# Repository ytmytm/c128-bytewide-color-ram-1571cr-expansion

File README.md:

# C128 8-bit Color RAM and C128DCR 1571CR RAM expansion

This is a 24 to 28 pin adapter PCB that can be used for three different C128 modifications:

- widen 2K Color RAM to 8 bits (C128/C128D/C128DCR)
- widen Color RAM to 8 bits and expand to 32K (C128/C128D/C128DCR)
- RAM Expansion for 1571CR compatible with Maverick (C128DCR only)

## Schematic

PDF plot of [the schematic can be found here](kicad/plots/kicad-c128-byte-wide-color-ram.pdf).

[kicad](kicad/) folder contains all the KiCad 6.0 project files.

## PCB

[kicad/plots](kicad/plots) folder contains Gerber files for manufacturing a PCB for any of these projects.

# 8-bit Color RAM

## Background

The idea comes from [a project published in 1990](http://www.sdiy.org/richardc64/color/byte.html).

All C128 variations use 8x2K SRAM chip (2016) for Color RAM. Although RAM is 8-bit, only lower 4 bits are connected. Lines D4-D7 are pulled up by a resistor pack to 5V.
This project replicates part of the onboard circuit and adds a quad switch 4066 as a bidirectional buffer between higher 4 bits and CPU bus.
Like the onboard U20 (4066) it switches Color RAM on/off bus, depending on the state of AEC line.

Note: this schematic shows the general idea. Don't cut anything on the mainboard and don't piggyback chips

## Why?

For sure it doesn't add any colors. However having 1K (2K in C128 mode) of additional RAM may be useful for some projects. It is compatible with any other expansion or cartidge.

## 32K option

Even more of that RAM? Possibilities are endless, but how to switch the banks?

VIC utilizes 1K of Color RAM, but C128 was equipped with double of that amount to support split screen multicolor graphics in BASIC. The bank switching between lower 1K and upper 1K is done using CPU port at location $01.
In C64 mode this port decides about RAM/ROM configuration, in C128 mode lower two bits determine which half of 2K Color RAM is seen by VIC and which half by CPU.

It only made sense to me to extend this further and use other $01 port bits to provide more address lines for 32K Color RAM expansion. None of my C128s will be ever used with tape (or even TapeCart), so I connected A11-13 lines to
lines normally used by tape motor control, tape write and sense bits. This provides 13 bits of address, so 16K total.

You don't need to connect all of them or you can skip it altogether. I have reused connections to onboard pull-up resistors to pull these address lines high if nothing is connecte to the solder pads.

Until I have a better idea where to connect A14 I will be happy with using 16K of that RAM. That's enough for 16 full screens: 8 for imaginary FLI mode with color ram switched every line and another 8 for interlaced option.

Note that a lot of C64 software will write to CPU port ($01) location and can modify the status of tape control bits. If you're not planning to use tape device I highly recommend patching the ROM (details below)
to set these bits as input by default. This completely removes the problem as virtually no software modifies CPU port direction register ($00).

## Assembly

Parts needed:

- 24-pin socket to be soldered in place of removed U19
- two sets of 12 round pins (24 total)
- 4066 analog quad switch and 14-pin socket for it
- 24-pin socket for 2K SRAM (2016) *or* 28-pin socket for 32K SRAM (62256)
- 8x2K RAM (ideally 2016 desoldered from the board) *or* 8x32K SRAM (62256)

In any case you need to remove or desolder the original 2K chip (U19) and replace it by a 24-pin socket. PCB is meant to be equipped with round pins and plugged into that socket.
We also need some signals from the board, so additional wires will be needed.

Start assembly by soldering in two rows of 24 round pins that will be used to plug in PCB to the C128/D/DCR mainboard.
For this project you need to solder them in the row of holes closest to the PCB edge and the one marked on silkscreen, on the image below marked by RED.

For 2K option solder the 24-pin socket in holes marked GREEN. For 32K option solder 28-pin socket in holes marked YELLOW.

The last step of the assembly is soldering in 14-pin socket for 4066.

## Installation

Once the assembled PCB is plugged into place of original SRAM (U19) (*mind the orientation*) you need to connect five additional wires to the mainboard:

- connect AEC from onboard U20 (4066) any pin 5, 6, 12 or 13 - they are all connected together
- connect D4-D7 in any order from charset ROM nearby or from convenient vias. You may have 24 or 28-pin ROM there, so check the pinout and verify against e.g. CPU

D4-D7 lines are on the right bottom end of the chip.

**Note:** if you don't have 2K SRAM chip or it was damaged during desoldering you can just pop in 32K SRAM chip (still available these days) and stop here.
If you look on the schematics I have routed onboard D4-D7 lines (pulled high by onboard resistors) to A11-A14 lines.
So if you don't connect there anything at all they will be driven high and even with 32K SRAM those 2K of Color RAM will be available with no extra connections.

## Installation (32K Color RAM)

- connect A11/A12/A13 to CPU tape ports P3/P4/P5 from CPU socket (pins 27/26/25) or from convenient vias

Like with data lines it doesn't really matter in which order you connect those tape motor/write/sense connections to solder points A11-A14 lines or even if you leave A11 or A14 unconnected.

I wanted to avoid soldering directly to CPU (or underneath CPU) even though I have it already socketed. Instead I found several vias for convenient access.

For C128/C128D I found it invaluable to open [C128 Neo project in KiCad](https://github.com/jgrip/open128) and highlight ports and their net (using `` key) to see where they cross the board sides.

Here is how it can look like on C128D. It's already a mess off wires on that machine but you get the general idea:

- YELLOW points show AEC connection to U20
- ORANGE points show A11/A12/A13 connections to two vias and one side of R4 resistor
- A14 is not connected to anything
- data lines D4-D7 are connected to character ROM adapter nearby

## Testing

In C128 mode in monitor try:

```
M FD800 FD8080
```

then edit some values and try issuing the command again. You should see that the top four bits (first hex digit) hold their value.

## Testing (32K Color RAM)

Extra address lines are controlled by CPU port. First let's switch them all to output (as tape sense is an input by default):

```
POKE 0, PEEK(0) OR (8+16+32)
```

Then try to put some colored text on screen and switch RAM banks back and forth by using various combinations of bits 3, 4 and 5

```
X = PEEK(1) AND 199
POKE 1, X
POKE 1, X OR 8
POKE 1, X OR (8+16)
POKE 1, X OR 32
...
```

## Patching ROM (32K Color RAM)

C64/128 ROM will set the CPU port direction register ($00) to value $2F. This sets up bits 5 and 3 as outputs because they control tape motor and tape write lines. However a lot of C64 software will write to CPU port ($01)
and modify bits 3/4/5 that we allocated to select Color RAM banks. This doesn't break anything but may cause flicker or random screen colors during some operations (e.g. decompressing) - as if Color RAM was faulty.

An easy way to fix this is to patch Kernal C64 and C128 to set $00 to make all bits 3/4/5 as inputs by default. This can be easy accomplished with a hex editor such as [HxD](https://mh-nexus.de/en/hxd/).

For a 32K ROM for C128DCR (U32), or C128D modified to use 32K chips, use this already patched file: [U32.complete.318023-02-patched.bin](rom/U32.complete.318023-02-patched.bin).

1. Dump from onboard chips (or download from [zimmers.net](http://www.zimmers.net/anonftp/pub/cbm/firmware/computers/c128/index.html) ROM appropriate to your C128: 16K for unmodified C128D or 32K for C128DCR

2. Use hex editor to patch the ROM - search for values `A9 2F 85 00` and replace `2F` by `07`. In American ROM (complete.318023-02.bin) that value appears at offsets:

- `$3DDA` - C64 Kernal soft reset (real address `$FDDA`)
- `$613D` - C128 Kernal soft reset (real address `$FE13D`)
- `$6250` - C128 Kernal GO64 (real address `$FE250`)

3. If you have JiffyDOS or a 64K ROM with a switch that value will appear three more times in the second 32K half of the ROM. Patch it as well from `2F` to `07`.

4. Save and flash into a new EEPROM to replace onboard ROM U32 (DCR)

## Patching VICE (32K Color RAM)

If you can recompile [VICE](https://vice-emu.sourceforge.io/) on your own, here is a patch to enable 32K Color RAM emulation.

[ytm-c128-colorram-expansion.patch](vice/ytm-c128-colorram-expansion.patch)

This is based off VICE 3.8 release (28 December 2023, revision 44935).

You will find new option in `Settings -> Machine -> Mode -> Miscellaneous -> Expand color RAM...`.

This can be passed also from command line via `-c128colorramexpansion` option.

# 1571CR RAM expansion

## Background

Since I already had this PCB, which also does 2K (24 pin) to 32K (28 pin) conversion I had a closer look on the second 2016 2K SRAM chip present on C128DCR board.

This is 1571 RAM. In standard configuration there are exactly 2K of SRAM in range $0000-$07FF, just like on 1541.

There are [several projects that expand RAM on external 1571 and 1541s](http://d81.de/CLD-RAMBOard/References.shtml), but I couldn't find anything for 1571CR (internal 1571 of C128DCR).

I found a [memory map on zimmers.net](http://www.zimmers.net/anonftp/pub/cbm/schematics/drives/new/1571/memorymap.txt)
that described $6000-$7FFF range as "RAM shadows", so I conducted an experiment.

I have removed U103 (2016 2K SRAM) and put in this place a 24 to 28 pin adapter for 62256 (32K SRAM) and I connected A11-A14 directly to U101 (6502 CPU).
It worked right away with no extra parts. I was able to copy disks with Maverick v5 RAMBoard nibbler.

After more testing I saw that RAM is actualy present also in $0800-$0FFF range. In both $0000-$0FFF and $6000-$7FFF ranges that provides a total of 12K available.

## Why?

The only purpose seems to be [Maverick v5 RAMBoard nibbler](https://csdb.dk/release/?id=18107). [DolphinDOS uses extra memory](https://e4aws.silverdr.com/projects/dolphindos3/) but there is no way to add a parallel port to 1571CR in a way DolphinDOS expects - all these VIA port lines are
already used.

In Maverick to go 'GCR Nibbler' option and choose 'RAMBoard'. In further settings choose $6000-$7FFF area for RAM.

## Assembly

Parts needed:

- 24-pin socket to be soldered in place of removed U103
- two sets of 12 round pins (24 total)
- 28-pin socket for 32K SRAM (62256)
- 8x32K SRAM (62256)

You need to remove or desolder the original 2K chip (U103) and replace it by a 24-pin socket. PCB is meant to be equipped with round pins and plugged into that socket.
We also need some signals from the board, so additional wires will be needed.

Start assembly by soldering in two rows of 24 round pins that will be used to plug in PCB to the C128DCR mainboard.

For this project you need to leave RED holes unoccupied and solder round pins in the middle row of holes from the PCB edge, on the image below marked by GREEN.

Solder 28-pin socket in holes marked YELLOW. You don't need to do anything about 14-pin 4066 either, that won't be used.

Here is how it looks like. Don't mind the orange and yellow wires. These are jumpers that I missed to route in the first version of the board. Current project has it already fixed.

## Installation

Once the assembled PCB is plugged into place of original SRAM (U103) (*mind the orientation*) you need to connect four additional wires to the mainboard: the new address lines.

In the prototype I soldered them directly to the CPU (U101) pins 20, 22, 23 and 24, but I don't like this solution in the long run:

There are four vias where these address lines can be found:

## Testing

You can use test program from [RAMBOard test/demo disk](media/ramboard.zip) (cached from http://d81.de/CLD-RAMBOard/refs/ramboard.zip). For whatever reason the test program works but disk copier doesn't.

If you have JiffyDOS, it's easy to use JiffyMon in C64 mode. It can be [downloaded from CSDB](https://csdb.dk/release/?id=16906) with [PDF manual available here](http://slark.me/c64-downloads/jiffymon-machine-language-monitor-users-guide.pdf)

Commands with asterisk will act on the default drive memory, like:
```
M* 6000 6080
```
or copy data between C128 and the drive - from range $6000-$6080 to $0400 (top of screen):
```
MR 6000 6080 0400
```
and back from computer to the drive:
```
MW 0400 0480 6000
```

Restart monitor with
```
SYS 64715
```

For actual disk copying get Maverick V5 and after choosing GCR Nibbler select RAMBOard option. Then set it up for RAM that starts at $6000.

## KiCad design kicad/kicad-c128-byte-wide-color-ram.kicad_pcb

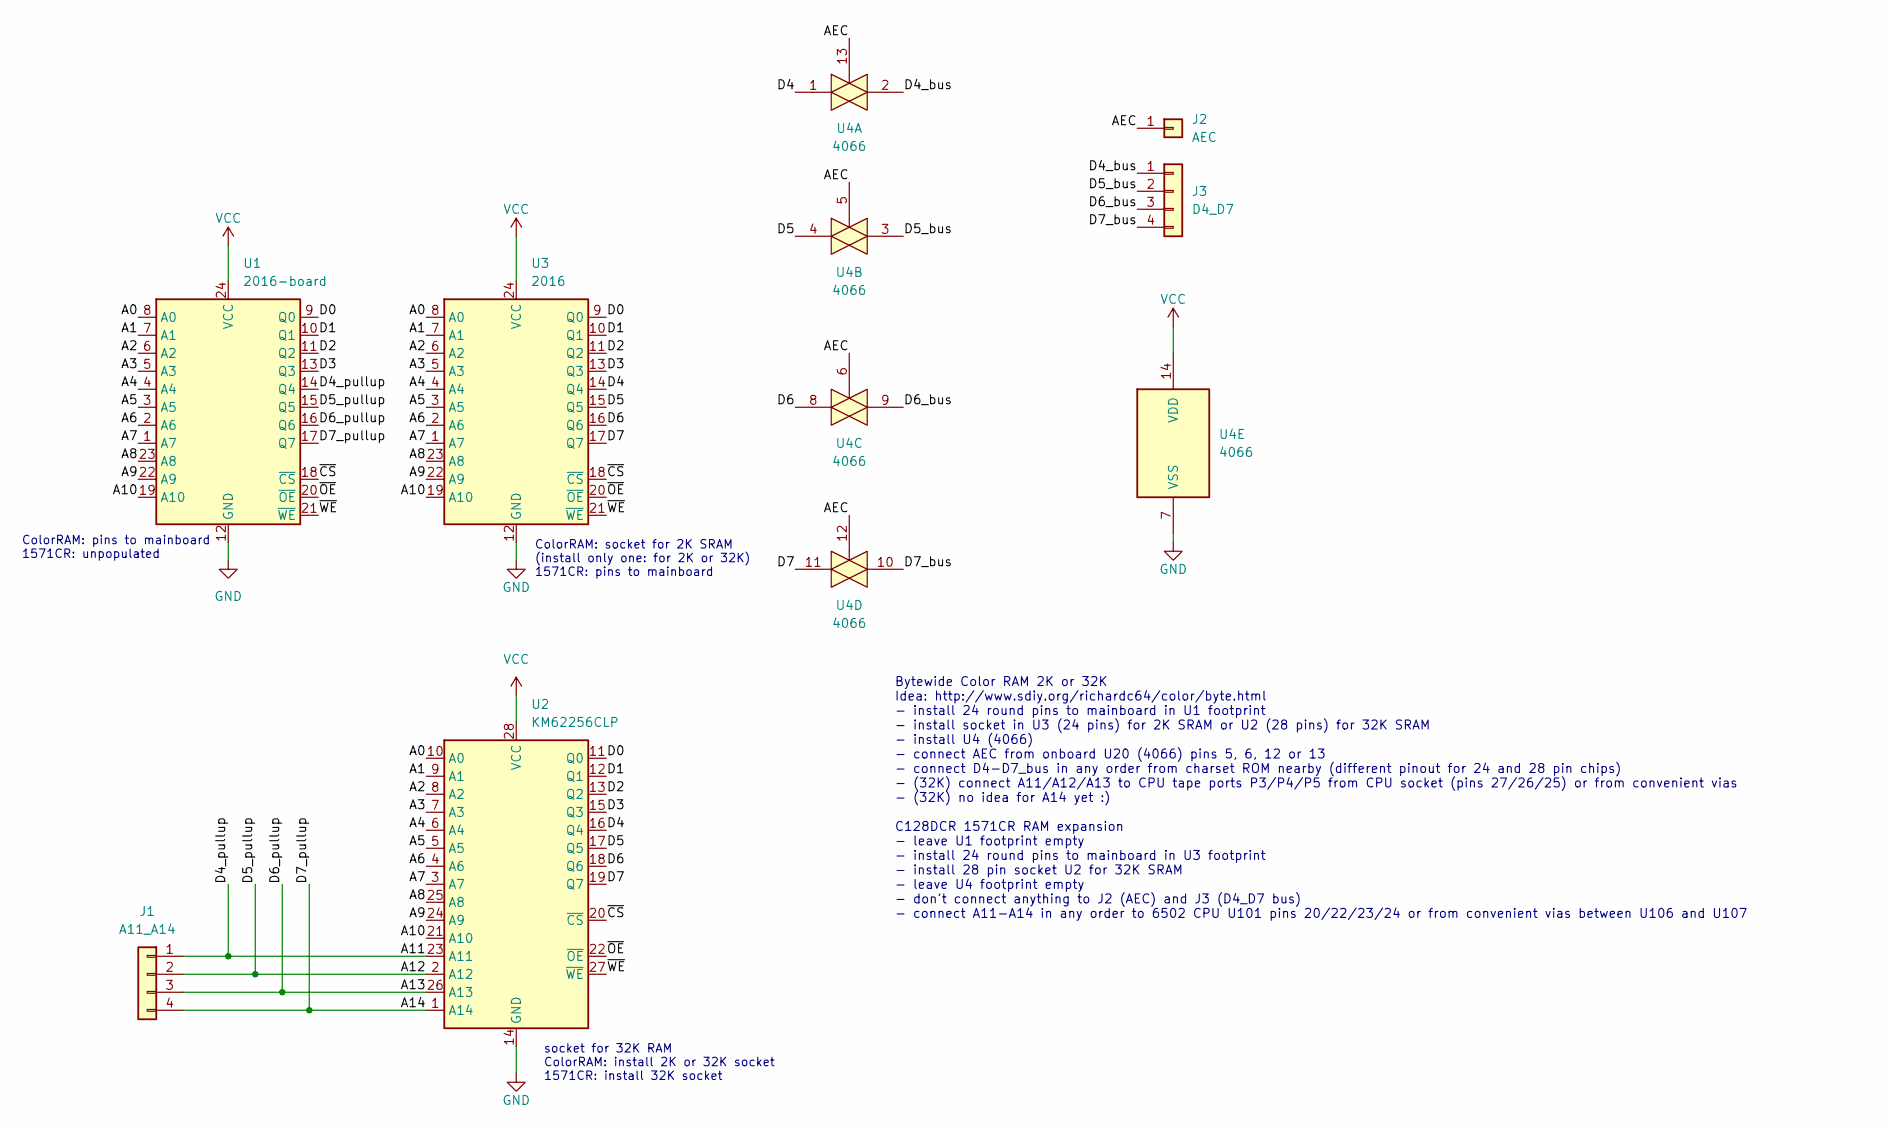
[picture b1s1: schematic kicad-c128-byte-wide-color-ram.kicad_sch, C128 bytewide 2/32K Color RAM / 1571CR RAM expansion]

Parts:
J1: A11_A14; PinHeader_1x04_P2.54mm_Vertical
J2: AEC; PinHeader_1x01_P2.54mm_Vertical
J3: D4_D7; PinHeader_1x04_P2.54mm_Vertical
U1: 2016-board; DIP-24_W15.24mm
U2: KM62256CLP; DIP-28_W15.24mm
U3: 2016; DIP-24_W15.24mm
U4: 4066; DIP-14_W7.62mm_Socket

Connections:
/A0: U1.8 (A0), U2.10 (A0), U3.8 (A0)
/A1: U1.7 (A1), U2.9 (A1), U3.7 (A1)
/A2: U1.6 (A2), U2.8 (A2), U3.6 (A2)
/A3: U1.5 (A3), U2.7 (A3), U3.5 (A3)
/A4: U1.4 (A4), U2.6 (A4), U3.4 (A4)
/A5: U1.3 (A5), U2.5 (A5), U3.3 (A5)
/A6: U1.2 (A6), U2.4 (A6), U3.2 (A6)
/A7: U1.1 (A7), U2.3 (A7), U3.1 (A7)
/A8: U1.23 (A8), U2.25 (A8), U3.23 (A8)
/A9: U1.22 (A9), U2.24 (A9), U3.22 (A9)
/A10: U1.19 (A10), U2.21 (A10), U3.19 (A10)
/A11: J1.1, U1.14 (Q4), U2.23 (A11)
/A12: J1.2, U1.15 (Q5), U2.2 (A12)
/A13: J1.3, U1.16 (Q6), U2.26 (A13)
/A14: J1.4, U1.17 (Q7), U2.1 (A14)
/AEC: J2.1, U4.5, U4.6, U4.12, U4.13
/D0: U1.9 (Q0), U2.11 (Q0), U3.9 (Q0)
/D1: U1.10 (Q1), U2.12 (Q1), U3.10 (Q1)
/D2: U1.11 (Q2), U2.13 (Q2), U3.11 (Q2)
/D3: U1.13 (Q3), U2.15 (Q3), U3.13 (Q3)
/D4: U2.16 (Q4), U3.14 (Q4), U4.1
/D4_bus: J3.1, U4.2
/D5: U2.17 (Q5), U3.15 (Q5), U4.4
/D5_bus: J3.2, U4.3
/D6: U2.18 (Q6), U3.16 (Q6), U4.8
/D6_bus: J3.3, U4.9
/D7: U2.19 (Q7), U3.17 (Q7), U4.11
/D7_bus: J3.4, U4.10
/~CS: U1.18 (~CS), U2.20 (~CS), U3.18 (~CS)
/~OE: U1.20 (~OE), U2.22 (~OE), U3.20 (~OE)
/~WE: U1.21 (~WE), U2.27 (~WE), U3.21 (~WE)
GND: U1.12 (GND), U2.14 (GND), U3.12 (GND), U4.7 (VSS)
VCC: U1.24 (VCC), U2.28 (VCC), U3.24 (VCC), U4.14 (VDD)

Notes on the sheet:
Bytewide Color RAM 2K or 32K Idea: http://www.sdiy.org/richardc64/color/byte.html - install 24 round pins to mainboard in U1 footprint - install socket in U3 (24 pins) for 2K SRAM or U2 (28 pins) for 32K SRAM - install U4 (4066) - connect AEC from onboard U20 (4066) pins 5, 6, 12 or 13 - connect D4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
ColorRAM: socket for 2K SRAM (install only one: for 2K or 32K) 1571CR: pins to mainboard
socket for 32K RAM ColorRAM: install 2K or 32K socket 1571CR: install 32K socket
ColorRAM: pins to mainboard 1571CR: unpopulated

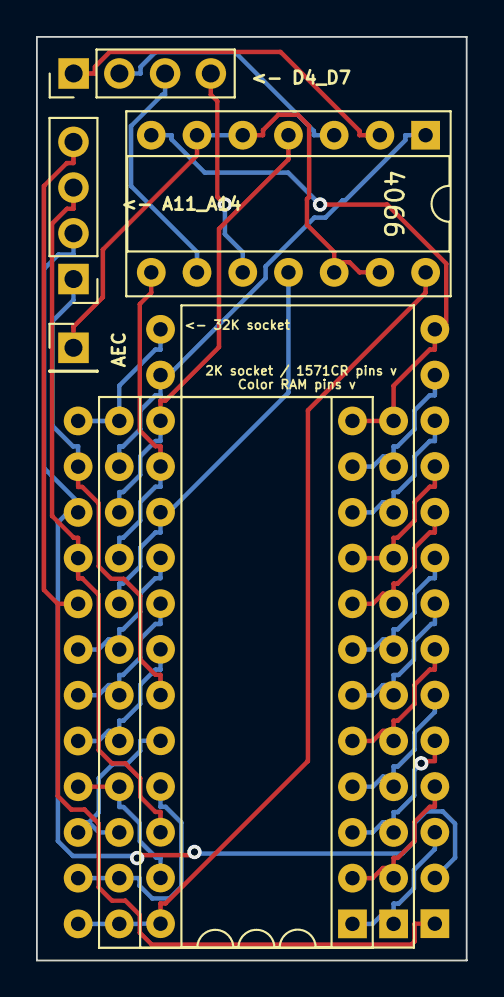
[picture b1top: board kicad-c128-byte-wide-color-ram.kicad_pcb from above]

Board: 2 copper layers, 23.9 x 51.3 mm, 7 parts (0 on the bottom side), 33 nets.

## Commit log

2023-10-24 initial commit, board printout fit tested to both c128d and c128dcr
2023-10-24 directory rename
2023-11-13 revision 1.1 with 1571CR info
2023-11-19 documentation
2023-11-20 corrected marks
2024-01-07 patched U32 ROM that makes CPU port bits 3/4/5 inputs by default
2024-01-07 VICE 3.8 patch on x128
